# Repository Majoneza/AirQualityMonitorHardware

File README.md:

# AirQualityMonitorHardware

Controller board for measuring indoor air quality with Bluetooth/WiFi connectivity
and an e-ink diplay output.

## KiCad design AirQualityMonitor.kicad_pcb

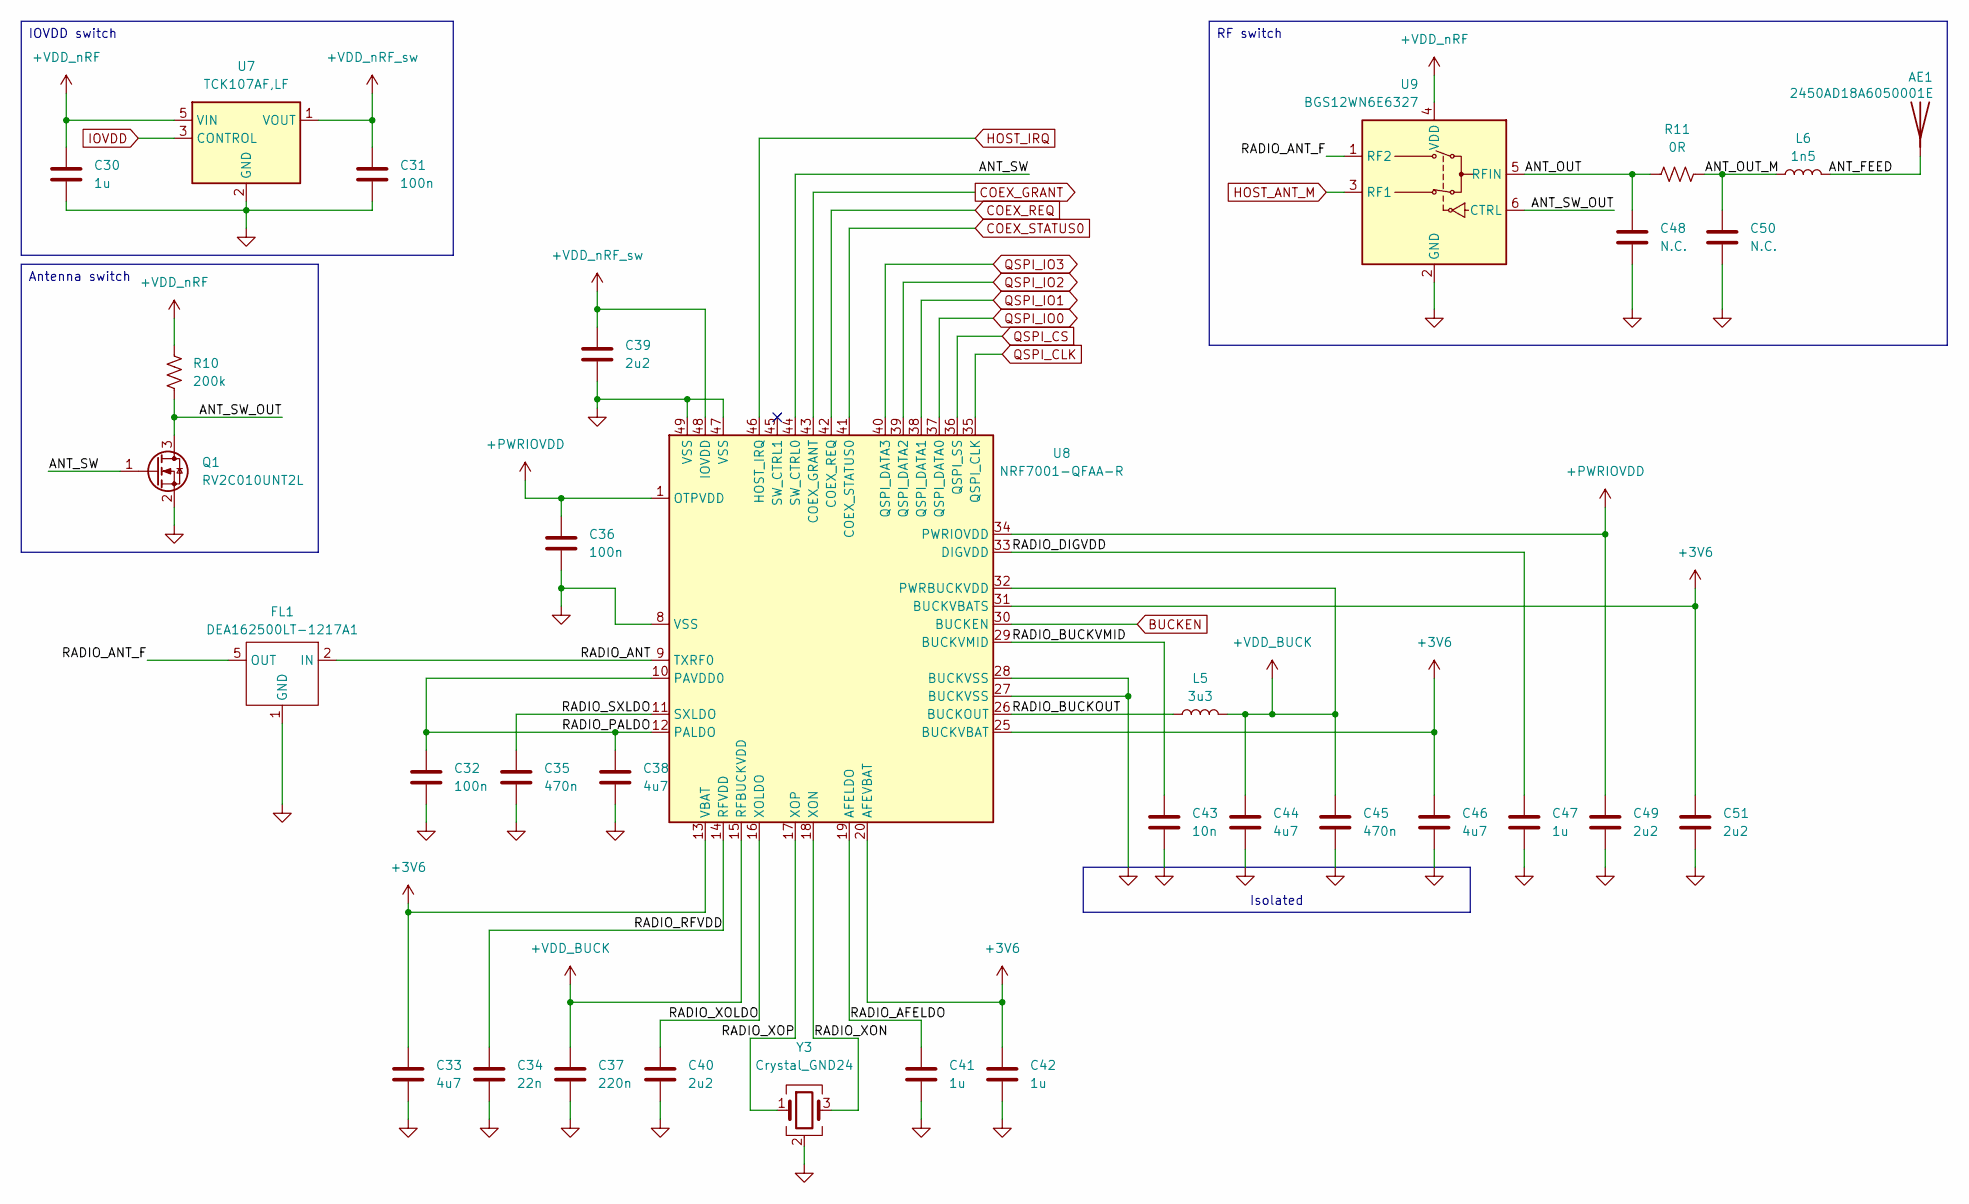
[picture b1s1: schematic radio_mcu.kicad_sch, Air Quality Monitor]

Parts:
AE1: 2450AD18A6050001E; ANTC3216X60N; Mouser Part Number 609-2450AD18A6050001
C30: 1u; C_0402_1005Metric; Manufacturer_Part_Number GRM155Z71A105KE01J; Mouser Part Number 81-GRM155Z71A105KE1J
C31: 100n; C_0603_1608Metric; Manufacturer_Part_Number GCJ188R71C104KA01D; Mouser Part Number 81-GCJ188R71C104KA1D
C32, C36: 100n; C_0201_0603Metric; Part 100nF 16VDC 10% 0201 X7S; Mouser Part Number 81-GRM033C71C104KE4J
C33, C38, C44, C46: 4u7; C_0603_1608Metric; Part 4.7uF 25VDC 10% 0603 X6S; Mouser Part Number 81-GRT188C81E475KE3D
C34: 22n; C_0201_0603Metric; Part 22nF 10VDC 10% 0201 X5R; Mouser Part Number 81-GRT033R61A223KE1J
C35, C45: 470n; C_0201_0603Metric; Part 470nF 6.3VDC 10% 0201 X5R; Mouser Part Number 81-GRM33R60J474KE90D
C37: 220n; C_0201_0603Metric; Part 220nF 10VDC 10% 0201 X5R; Mouser Part Number 81-GRM33R61A224KE90D
C39, C49, C51: 2u2; C_0603_1608Metric; Part 2.2uF 16VDC 10% 0603 X7R; Mouser Part Number 81-GRM188Z71C225KE3D
C40: 2u2; C_0201_0603Metric; Part 2.2uF 10VDC 10% 0201 X5R; Mouser Part Number 81-GRM033R61A225KE7D
C41, C42, C47: 1u; C_0402_1005Metric; Part 1uF 16VDC 10% 0402 X7R; Mouser Part Number 81-GRM155Z71A105KE1J
C43: 10n; C_0201_0603Metric; Part 10nF 16VDC 10% 0201 X7R; Mouser Part Number 81-GRM033R71C103KE4J
C48, C50: N.C.; C_0201_0603Metric
FL1: DEA162500LT-1217A1; DEA162500LT1217A1; Mouser Part Number 810-DEA16250LT1217A1
L5: 3u3; L_1008_2520Metric; Manufacturer_Part_Number LQM2HPN3R3MJ0L; Mouser Part Number 81-LQM2HPN3R3MJ0L
L6: 1n5; L_0201_0603Metric; Manufacturer_Part_Number LQP03HQ1N5B02D; Mouser Part Number 81-LQP03HQ1N5B02D
Q1: RV2C010UNT2L; Manufacturer_Part_Number RV2C010UNT2L; Mouser Part Number 755-RV2C010UNT2L
R10: 200k; R_0805_2012Metric; Manufacturer_Part_Number AC0805FR-7W200KL; Mouser Part Number 603-AC0805FR-7W200KL
R11: 0R; R_0201_0603Metric; Manufacturer_Part_Number RC0201FR-070RL; Mouser Part Number 603-RC0201FR-070RL
U7: TCK107AF,LF; SMV_1; Mouser Part Number 757-TCK107AFLF
U8: NRF7001-QFAA-R; QFN-48-1EP_6x6mm_P0.4mm_EP4.66x4.66mm; Mouser Part Number 949-NRF7001-QFAA-R
U9: BGS12WN6E6327; Infineon_PG-TSNP-6-10_0.7x1.1mm_0.7x1.1mm_P0.4mm; Manufacturer_Part_Number BGS12WN6E6327XTSA1; Mouser Part Number 726-BGS12WN6E6327XTS
Y3: Crystal_GND24; Crystal_SMD_1612-4Pin_1.6x1.2mm; Manufacturer_Part_Number ECS-400-8-47-JTN-TR; Mouser Part Number 520-ECS-400-8-47JTNT

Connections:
+3V6: C33.1, C42.1, C46.1, C51.1, U8.13 (VBAT), U8.20 (AFEVBAT), U8.25 (BUCKVBAT), U8.31 (BUCKVBATS); also elsewhere on the board
+PWRIOVDD: C36.1, C49.1, U8.1 (OTPVDD), U8.34 (PWRIOVDD)
+VDDIO: C30.1, R10.2, U7.5 (VIN), U9.4 (VDD); also elsewhere on the board
+VDD_BUCK: C37.1, C44.1, C45.1, L5.2, U8.15 (RFBUCKVDD), U8.32 (PWRBUCKVDD)
+VDD_nRF_sw: C31.1, C39.1, U7.1 (VOUT), U8.48 (IOVDD)
/Radio MCU/ANT_FEED: AE1.1 (A_1), L6.2
/Radio MCU/ANT_OUT: C48.1, R11.1, U9.5 (RFIN)
/Radio MCU/ANT_OUT_M: C50.1, L6.1, R11.2
/Radio MCU/ANT_SW: Q1.1 (G), U8.44 (SW_CTRL0)
/Radio MCU/ANT_SW_OUT: Q1.3 (D), R10.1, U9.6 (CTRL)
/Radio MCU/RADIO_AFELDO: C41.1, U8.19 (AFELDO)
/Radio MCU/RADIO_ANT: FL1.2 (IN), U8.9 (TXRF0)
/Radio MCU/RADIO_ANT_F: FL1.5 (OUT), U9.1 (RF2)
/Radio MCU/RADIO_BUCKOUT: L5.1, U8.26 (BUCKOUT)
/Radio MCU/RADIO_BUCKVMID: C43.1, U8.29 (BUCKVMID)
/Radio MCU/RADIO_DIGVDD: C47.1, U8.33 (DIGVDD)
/Radio MCU/RADIO_PALDO: C32.1, C38.1, U8.10 (PAVDD0), U8.12 (PALDO)
/Radio MCU/RADIO_RFVDD: C34.1, U8.14 (RFVDD)
/Radio MCU/RADIO_SXLDO: C35.1, U8.11 (SXLDO)
/Radio MCU/RADIO_XOLDO: C40.1, U8.16 (XOLDO)
/Radio MCU/RADIO_XON: U8.18 (XON), Y3.3
/Radio MCU/RADIO_XOP: U8.17 (XOP), Y3.1
BUCKEN: U8.30 (BUCKEN); also elsewhere on the board
COEX_GRANT: U8.43 (COEX_GRANT); also elsewhere on the board
COEX_REQ: U8.42 (COEX_REQ); also elsewhere on the board
COEX_STATUS0: U8.41 (COEX_STATUS0); also elsewhere on the board
GND: C30.2, C31.2, C32.2, C33.2, C34.2, C35.2, C36.2, C37.2, C38.2, C39.2, C40.2, C41.2, C42.2, C43.2, C44.2, C45.2, C46.2, C47.2, C48.2, C49.2, C50.2, C51.2, FL1.1 (GND), FL1.3 (GND), FL1.4 (GND), FL1.6 (GND), Q1.2 (S), U7.2 (GND), U8.8 (VSS), U8.27 (BUCKVSS), U8.28 (BUCKVSS), U8.47 (VSS), U8.49 (VSS), U9.2 (GND), Y3.2 (G), Y3.4 (G); also elsewhere on the board
HOST_ANT_M: U9.3 (RF1); also elsewhere on the board
HOST_IRQ: U8.46 (HOST_IRQ); also elsewhere on the board
IOVDD: U7.3 (CONTROL); also elsewhere on the board
QSPI_CLK: U8.35 (QSPI_CLK); also elsewhere on the board
QSPI_CS: U8.36 (QSPI_SS); also elsewhere on the board
QSPI_IO0: U8.37 (QSPI_DATA0); also elsewhere on the board
QSPI_IO1: U8.38 (QSPI_DATA1); also elsewhere on the board
QSPI_IO2: U8.39 (QSPI_DATA2); also elsewhere on the board
QSPI_IO3: U8.40 (QSPI_DATA3); also elsewhere on the board

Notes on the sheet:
RF switch
Antenna switch
Isolated
IOVDD switch

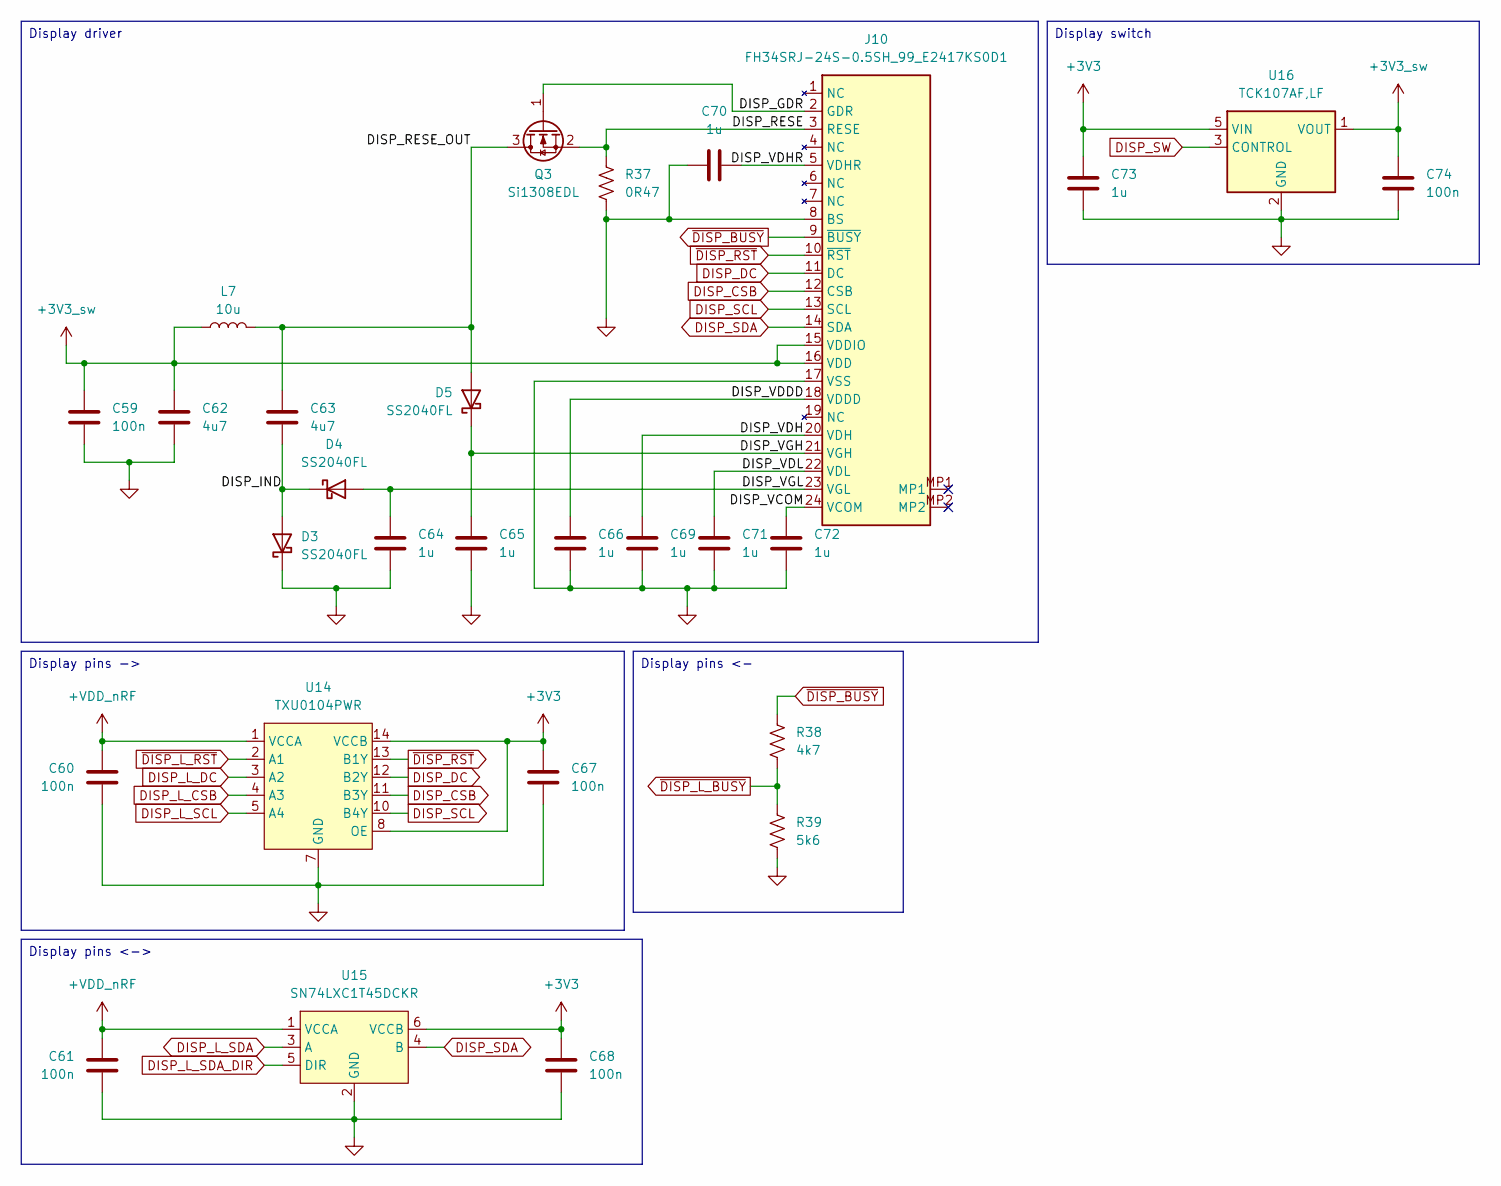
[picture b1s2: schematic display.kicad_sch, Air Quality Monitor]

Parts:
C59: 100n; C_0603_1608Metric; Part 100nF 16VDC 10% 0603 X7R; Mouser Part Number 81-GCJ188R71C104KA1D
C60, C61, C67, C68, C74: 100n; C_0603_1608Metric; Manufacturer_Part_Number GCJ188R71C104KA01D; Mouser Part Number 81-GCJ188R71C104KA1D
C62, C63: 4u7; C_0603_1608Metric; Part 4.7uF 25VDC 10% 0603 X6S; Mouser Part Number 81-GRT188C81E475KE3D
C64, C65, C66, C69, C70, C71, C72: 1u; C_0603_1608Metric; Part 1uF 25VDC 10% 0603 X5R; Mouser Part Number 603-CC603KRX5R8BB105
C73: 1u; C_0402_1005Metric; Manufacturer_Part_Number GRM155Z71A105KE01J; Mouser Part Number 81-GRM155Z71A105KE1J
D3, D4, D5: SS2040FL; D_SOD-123F; Manufacturer_Part_Number SS2040FL_R1_00001; Mouser Part Number 241-SS2040FLR100001
J10: FH34SRJ-24S-0.5SH_99_E2417KS0D1; FH34SRJ24S05SH99; Mouser Part Number 798-FH34SRJ24S05SH99
L7: 10u; L_1008_2520Metric; Manufacturer_Part_Number AOTA-N252010S-100MT; Mouser Part Number 815-AOTAN252010S100M
Q3: Si1308EDL; SOT-323_SC-70; Manufacturer_Part_Number SI1308EDL-T1-GE3; Mouser Part Number 78-SI1308EDL-T1-GE3
R37: 0R47; R_0603_1608Metric; Manufacturer_Part_Number RCWL0603R470JNEA; Mouser Part Number 71-RCWL0603R470JNEA
R38: 4k7; R_0402_1005Metric; Manufacturer_Part_Number RC0402JR-104K7L; Mouser Part Number 603-RC0402JR-104K7L
R39: 5k6; R_0402_1005Metric; Manufacturer_Part_Number RC0402JR-075K6L; Mouser Part Number 603-RC0402JR-075K6L
U14: TXU0104PWR; TSSOP-14_4.4x5mm_P0.65mm; Mouser Part Number 595-TXU0104PWR
U15: SN74LXC1T45DCKR; SOT-363_SC-70-6; Mouser Part Number 595-SN74LXC1T45DCKR
U16: TCK107AF,LF; SMV_1; Mouser Part Number 757-TCK107AFLF

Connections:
+3V3: C67.1, C68.1, C73.1, U14.8 (OE), U14.14 (VCCB), U15.6 (VCCB), U16.5 (VIN); also elsewhere on the board
+3V3_sw: C59.1, C62.1, C74.1, J10.15 (VDDIO), J10.16 (VDD), L7.1, U16.1 (VOUT)
+VDDIO: C60.1, C61.1, U14.1 (VCCA), U15.1 (VCCA); also elsewhere on the board
/Display/DISP_GDR: J10.2 (GDR), Q3.1 (G)
/Display/DISP_IND: C63.2, D3.2 (A), D4.1 (K)
/Display/DISP_RESE: J10.3 (RESE), Q3.2 (S), R37.1
/Display/DISP_RESE_OUT: C63.1, D5.2 (A), L7.2, Q3.3 (D)
/Display/DISP_VCOM: C72.1, J10.24 (VCOM)
/Display/DISP_VDDD: C66.1, J10.18 (VDDD)
/Display/DISP_VDH: C69.1, J10.20 (VDH)
/Display/DISP_VDHR: C70.2, J10.5 (VDHR)
/Display/DISP_VDL: C71.1, J10.22 (VDL)
/Display/DISP_VGH: C65.1, D5.1 (K), J10.21 (VGH)
/Display/DISP_VGL: C64.1, D4.2 (A), J10.23 (VGL)
DISP_CSB: J10.12 (CSB), U14.11 (B3Y)
DISP_DC: J10.11 (DC), U14.12 (B2Y)
DISP_L_CSB: U14.4 (A3); also elsewhere on the board
DISP_L_DC: U14.3 (A2); also elsewhere on the board
DISP_L_SCL: U14.5 (A4); also elsewhere on the board
DISP_L_SDA: U15.3 (A); also elsewhere on the board
DISP_L_SDA_DIR: U15.5 (DIR); also elsewhere on the board
DISP_SCL: J10.13 (SCL), U14.10 (B4Y)
DISP_SDA: J10.14 (SDA), U15.4 (B)
DISP_SW: U16.3 (CONTROL); also elsewhere on the board
GND: C59.2, C60.2, C61.2, C62.2, C64.2, C65.2, C66.2, C67.2, C68.2, C69.2, C70.1, C71.2, C72.2, C73.2, C74.2, D3.1 (K), J10.8 (BS), J10.17 (VSS), R37.2, R39.2, U14.7 (GND), U15.2 (GND), U16.2 (GND); also elsewhere on the board
~DISP_BUSY: J10.9 (~BUSY), R38.1
~DISP_L_BUSY: R38.2, R39.1; also elsewhere on the board
~DISP_L_RST: U14.2 (A1); also elsewhere on the board
~DISP_RST: J10.10 (~RST), U14.13 (B1Y)

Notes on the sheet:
Display pins <->
Display pins ->
Display pins <-
Display driver
Display switch

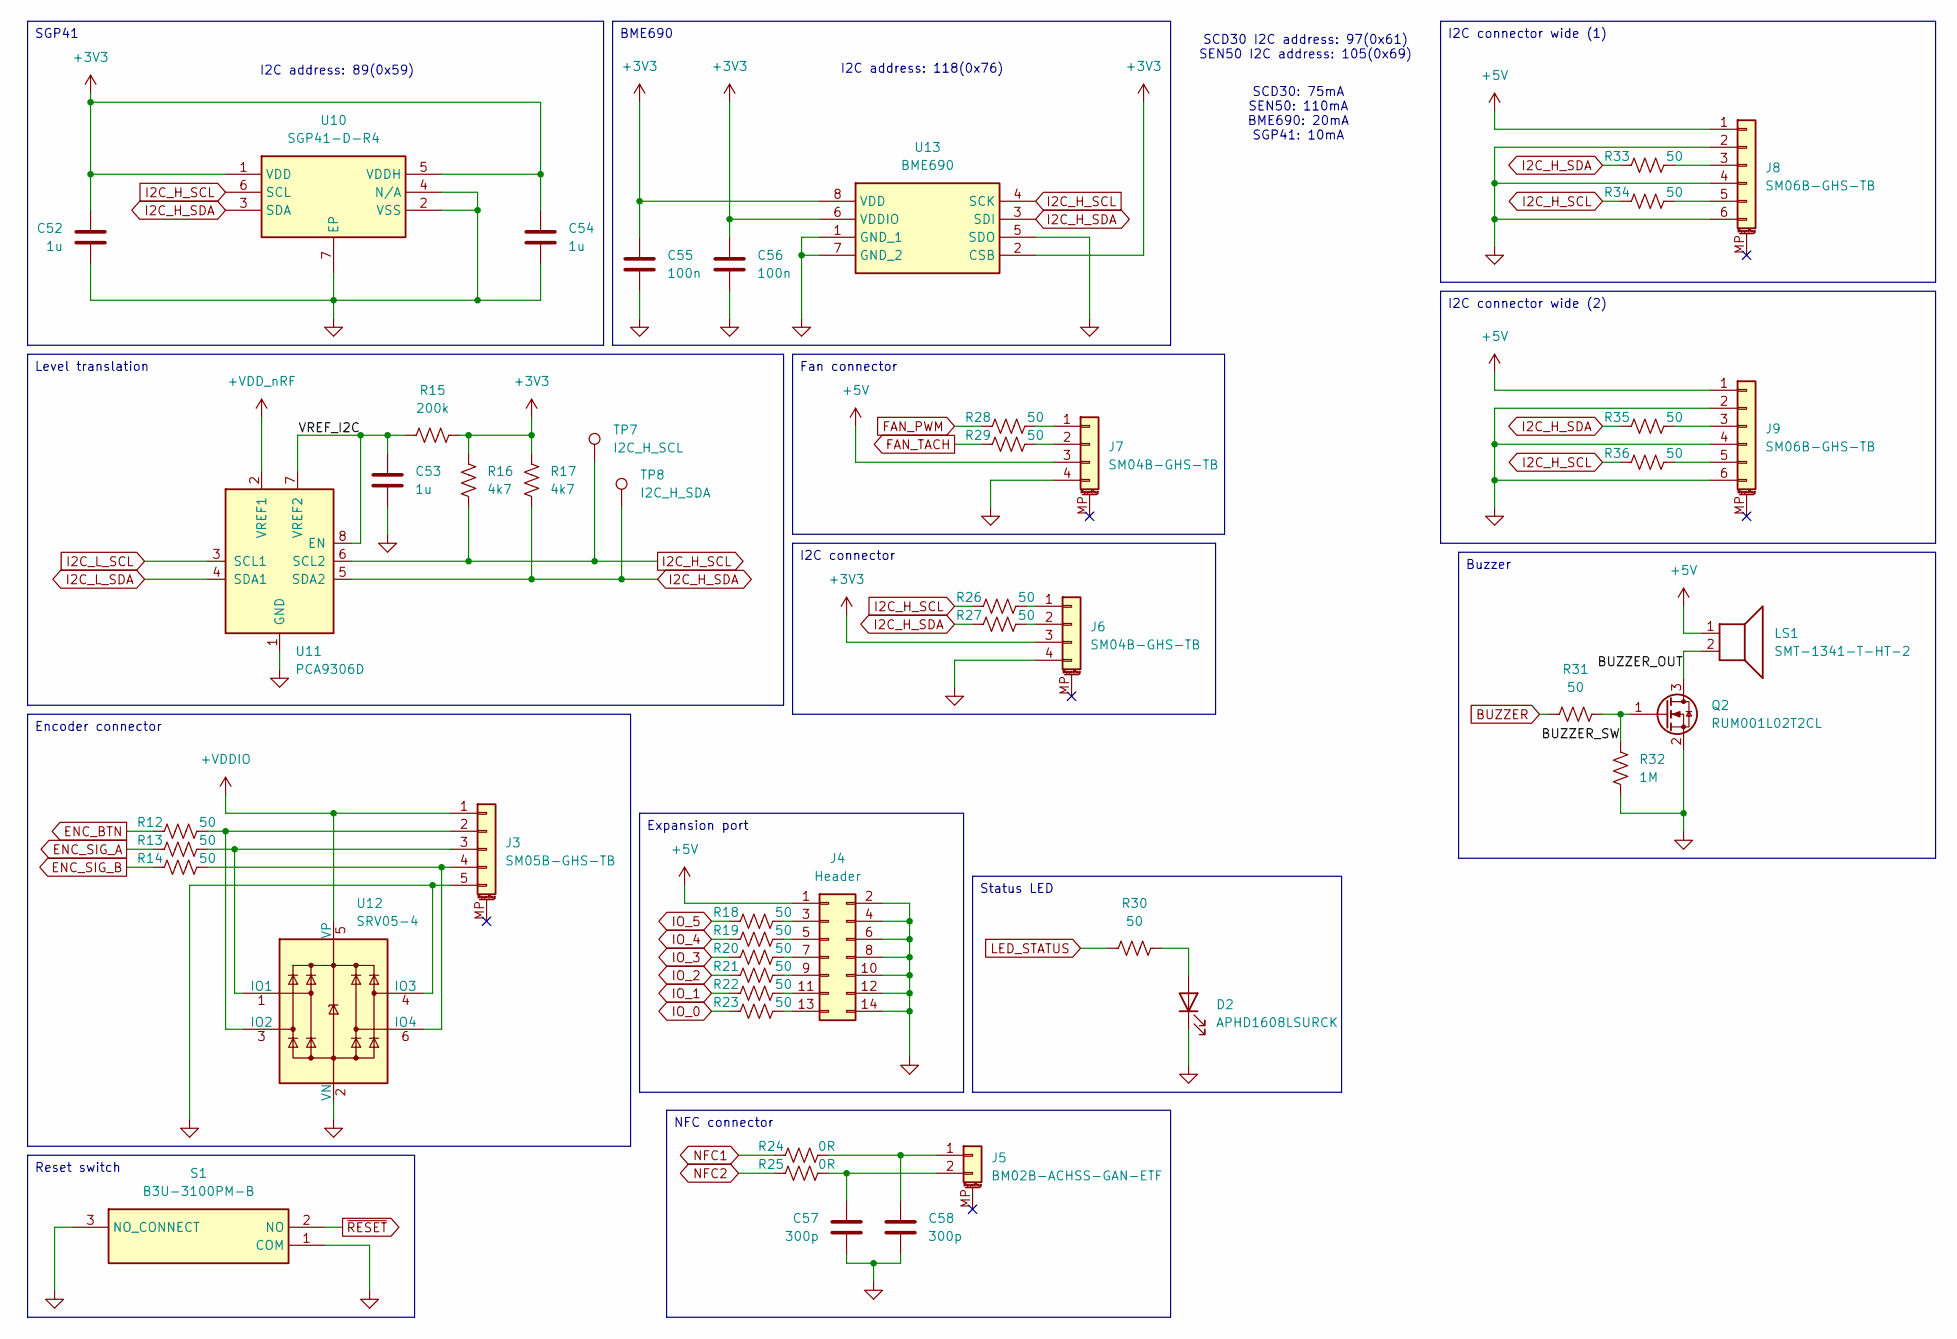
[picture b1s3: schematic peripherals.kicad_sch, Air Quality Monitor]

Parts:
C52, C53, C54: 1u; C_0402_1005Metric; Manufacturer_Part_Number GRM155Z71A105KE01J; Mouser Part Number 81-GRM155Z71A105KE1J
C55, C56: 100n; C_0201_0603Metric; Part 100nF 16VDC 10% 0201 X7S; Mouser Part Number 81-GRM033C71C104KE4J
C57, C58: 300p; C_0402_1005Metric; Manufacturer_Part_Number GRM1555C1H301JA01D; Mouser Part Number 81-GRM1555C1H301JA1D
D2: APHD1608LSURCK; LED_0603_1608Metric; Mouser Part Number 604-APHD1608LSURCK
J3: SM05B-GHS-TB; JST_GH_SM05B-GHS-TB_1x05-1MP_P1.25mm_Horizontal; Manufacturer_Part_Number SM05B-GHS-TB(LF)(SN); Mouser Part Number 306-SM05BGHSTBLFSN
J4: Header; PinSocket_2x07_P1.27mm_Vertical_SMD
J5: BM02B-ACHSS-GAN-ETF; JST_ACH_BM02B-ACHSS-GAN-ETF_1x02-1MP_P1.20mm_Vertical; Manufacturer_Part_Number BM02B-ACHSS-GAN-ETF(LF)(SN); Mouser Part Number 306-2BACHSSGANETFL
J6, J7: SM04B-GHS-TB; JST_GH_SM04B-GHS-TB_1x04-1MP_P1.25mm_Horizontal; Manufacturer_Part_Number SM04B-GHS-TB(LF)(SN); Mouser Part Number 306-SM04BGHSTBLFSN
J8, J9: SM06B-GHS-TB; JST_GH_SM06B-GHS-TB_1x06-1MP_P1.25mm_Horizontal; Manufacturer_Part_Number SM06B-GHS-TB(LF)(SN); Mouser Part Number 306-SM06BGHSTBLFSN
LS1: SMT-1341-T-HT-2; SMT1341THT2; Mouser Part Number 665-SMT-1341-T-HT-2
Q2: RUM001L02T2CL; SOT723; Mouser Part Number 755-RUM001L02T2CL
R12, R13, R14, R18, R19, R20, R21, R22, R23, R26, R27, R28, R29, R30, R31, R33, R34, R35, R36: 50; R_0402_1005Metric; Manufacturer_Part_Number RC0402JR-0750RL; Mouser Part Number 603-RC0402JR-0750RL
R15: 200k; R_0805_2012Metric; Manufacturer_Part_Number AC0805FR-7W200KL; Mouser Part Number 603-AC0805FR-7W200KL
R16, R17: 4k7; R_0402_1005Metric; Manufacturer_Part_Number RC0402JR-104K7L; Mouser Part Number 603-RC0402JR-104K7L
R24, R25: 0R; R_0603_1608Metric; Manufacturer_Part_Number ERJ-S030R00V; Mouser Part Number 667-ERJ-S030R00V
R32: 1M; R_0603_1608Metric; Manufacturer_Part_Number RT0603BRD071ML; Mouser Part Number 603-RT0603BRD071ML
S1: B3U-3100PM-B; B3U3100PMB; Mouser Part Number 653-B3U-3100PM-B
TP7: I2C_H_SCL; TestPoint_Pad_D1.0mm
TP8: I2C_H_SDA; TestPoint_Pad_D1.0mm
U10: SGP41-D-R4; SON80P244X244X95-7N; Mouser Part Number 403-SGP41-D-R4
U11: PCA9306D; TSSOP-8_3x3mm_P0.65mm; Manufacturer_Part_Number PCA9306DP,118; Mouser Part Number 771-PCA9306DP-T
U12: SRV05-4; SOT-23-6; Manufacturer_Part_Number SRV05-4.TCT; Mouser Part Number 947-SRV05-4.TCT
U13: BME690; Mouser Part Number 262-BME690

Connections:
+3V3: C52.1, C54.1, C55.1, C56.1, J6.3, R15.2, R16.1, R17.1, U10.1 (VDD), U10.5 (VDDH), U13.2 (CSB), U13.6 (VDDIO), U13.8 (VDD); also elsewhere on the board
+5V: J4.1, J7.3, J8.1, J9.1, LS1.1; also elsewhere on the board
+VDDIO: J3.1, U11.2 (VREF1), U12.5 (VP); also elsewhere on the board
/Peripherals/BUZZER_OUT: LS1.2, Q2.3 (D)
/Peripherals/BUZZER_SW: Q2.1 (G), R31.2, R32.2
/Peripherals/VREF_I2C: C53.1, R15.1, U11.7 (VREF2), U11.8 (EN)
BUZZER: R31.1; also elsewhere on the board
ENC_BTN: R12.1; also elsewhere on the board
ENC_SIG_A: R13.1; also elsewhere on the board
ENC_SIG_B: R14.1; also elsewhere on the board
FAN_PWM: R28.1; also elsewhere on the board
FAN_TACH: R29.1; also elsewhere on the board
GND: C52.2, C53.2, C54.2, C55.2, C56.2, C57.2, C58.2, D2.1 (K), J3.5, J4.2, J4.4, J4.6, J4.8, J4.10, J4.12, J4.14, J6.4, J7.4, J8.2, J8.4, J8.6, J9.2, J9.4, J9.6, Q2.2 (S), R32.1, S1.1 (COM), S1.3 (NO_CONNECT), U10.2 (VSS), U10.4 (N/A), U10.7 (EP), U11.1 (GND), U12.2 (VN), U12.4 (IO3), U13.1 (GND_1), U13.5 (SDO), U13.7 (GND_2); also elsewhere on the board
I2C_H_SCL: R16.2, R26.1, R34.1, R36.1, TP7.1 (1_1), U10.6 (SCL), U11.6 (SCL2), U13.4 (SCK)
I2C_H_SDA: R17.2, R27.1, R33.1, R35.1, TP8.1 (1_1), U10.3 (SDA), U11.5 (SDA2), U13.3 (SDI)
I2C_L_SCL: U11.3 (SCL1); also elsewhere on the board
I2C_L_SDA: U11.4 (SDA1); also elsewhere on the board
IO_0: R23.1; also elsewhere on the board
IO_1: R22.1; also elsewhere on the board
IO_2: R21.1; also elsewhere on the board
IO_3: R20.1; also elsewhere on the board
IO_4: R19.1; also elsewhere on the board
IO_5: R18.1; also elsewhere on the board
LED_STATUS: R30.1; also elsewhere on the board
NFC1: R24.1; also elsewhere on the board
NFC2: R25.1; also elsewhere on the board
unnamed: D2.2 (A), R30.2
unnamed: J3.2, R12.2, U12.3 (IO2)
unnamed: J3.3, R13.2, U12.1 (IO1)
unnamed: J3.4, R14.2, U12.6 (IO4)
unnamed: J4.3, R18.2
unnamed: J4.5, R19.2
unnamed: J4.7, R20.2
unnamed: J4.9, R21.2
unnamed: J4.11, R22.2
unnamed: J4.13, R23.2
unnamed: C58.1, J5.1, R24.2
unnamed: C57.1, J5.2, R25.2
unnamed: J6.1, R26.2
unnamed: J6.2, R27.2
unnamed: J7.1, R28.2
unnamed: J7.2, R29.2
unnamed: J8.3, R33.2
unnamed: J8.5, R34.2
unnamed: J9.3, R35.2
unnamed: J9.5, R36.2
~RESET: S1.2 (NO); also elsewhere on the board

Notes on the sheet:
SCD30 I2C address: 97(0x61) SEN50 I2C address: 105(0x69)
I2C address: 118(0x76)
SCD30: 75mA SEN50: 110mA BME690: 20mA SGP41: 10mA
I2C address: 89(0x59)
Encoder connector
Reset switch
Buzzer
Level translation
SGP41
I2C connector
Status LED
NFC connector
I2C connector wide (2)
Fan connector
Expansion port
BME690
I2C connector wide (1)

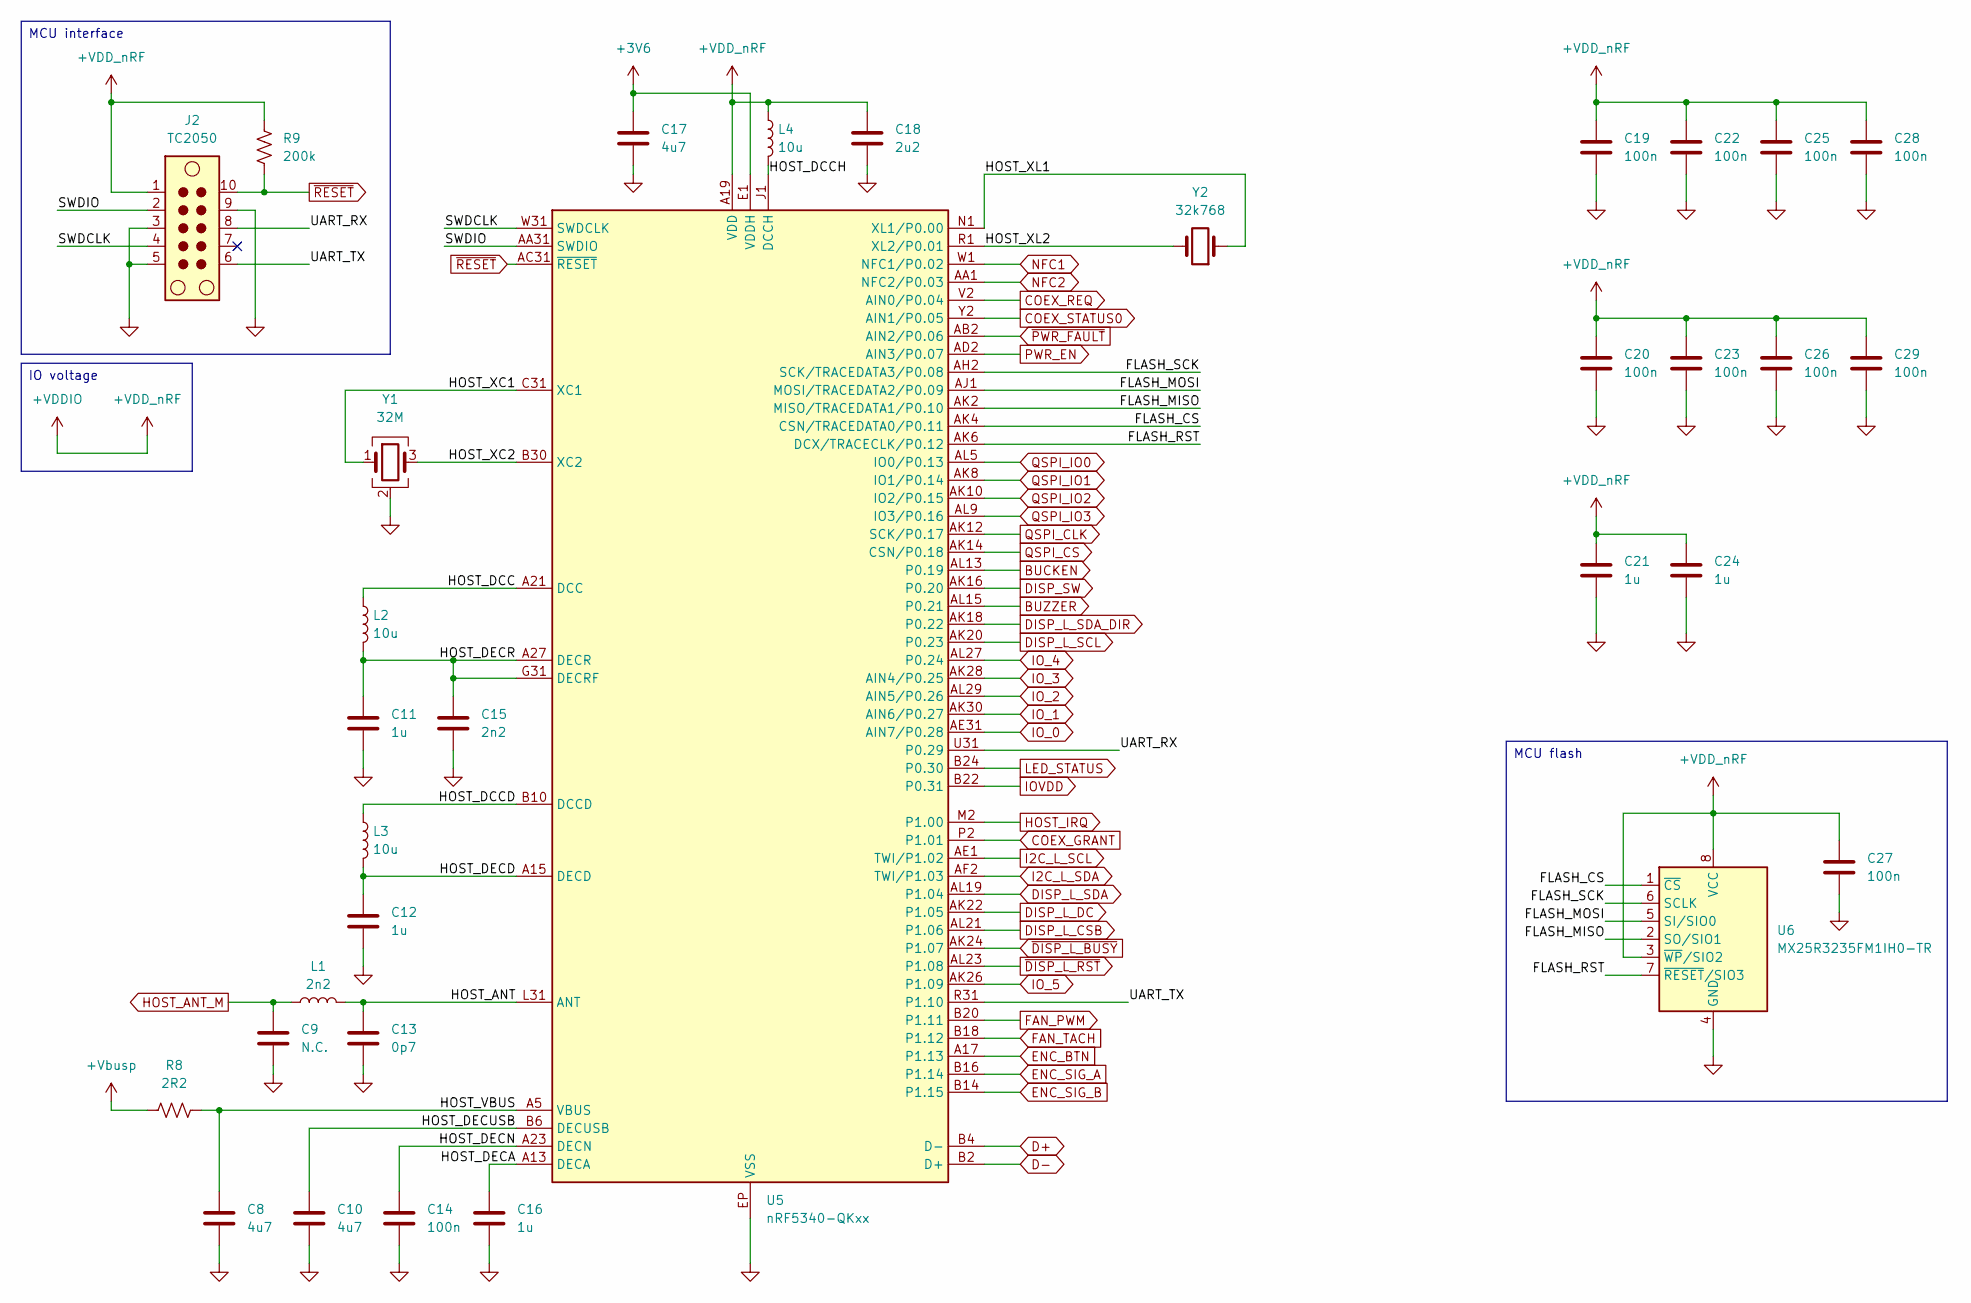
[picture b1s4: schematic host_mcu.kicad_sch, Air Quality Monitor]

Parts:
C8, C10, C17: 4u7; C_0603_1608Metric; Part 4.7uF 16VDC 10% 0603 X7R; Mouser Part Number 81-GRM188Z71C475KE1J
C9: N.C.; C_0201_0603Metric
C11, C12, C16, C21, C24: 1u; C_0402_1005Metric; Part 1uF 16VDC 10% 0402 X7R; Mouser Part Number 81-GRM155Z71A105KE1J
C13: 0p7; C_0201_0603Metric; Part 0.7pF 25VDC 8% 0201 NP0; Mouser Part Number 603-CQ201ARNPO8BNR70
C14, C19, C20, C22, C23, C25, C26, C27, C28, C29: 100n; C_0201_0603Metric; Part 100nF 16VDC 10% 0201 X7S; Mouser Part Number 81-GRM033C71C104KE4J
C15: 2n2; C_0201_0603Metric; Part 2.2nF 16VDC 10% 0201 X7R; Mouser Part Number 603-CC201KRX7R7BB222
C18: 2u2; C_0603_1608Metric; Part 2.2uF 16VDC 10% 0603 X7R; Mouser Part Number 81-GRM188Z71C225KE3D
J2: TC2050; Tag-Connect_TC2050-IDC-FP_2x05_P1.27mm_Vertical
L1: 2n2; L_0201_0603Metric; Manufacturer_Part_Number L02012R2BHSTR; Mouser Part Number 581-L02012R2BHSTR
L2, L3, L4: 10u; L_0603_1608Metric; Manufacturer_Part_Number MLZ1608E100MT; Mouser Part Number 810-MLZ1608E100MT
R8: 2R2; R_0201_0603Metric; Manufacturer_Part_Number AC0201FR-072R2L; Mouser Part Number 603-AC0201FR-072R2L
R9: 200k; R_0805_2012Metric; Manufacturer_Part_Number AC0805FR-7W200KL; Mouser Part Number 603-AC0805FR-7W200KL
U5: nRF5340-QKxx; Nordic_AQFN-94-1EP_7x7mm_P0.4mm; Manufacturer_Part_Number nRF5340-QKAA-R7; Mouser Part Number 949-NRF5340-QKAA-R7
U6: MX25R3235FM1IH0-TR; JEITA_SOIC-8_3.9x4.9mm_P1.27mm; Manufacturer_Part_Number MX25R3235FM1IH0-TR; Mouser Part Number 95-25R3235FM1IH0TR
Y1: 32M; Crystal_SMD_2016-4Pin_2.0x1.6mm; Manufacturer_Part_Number ECS-320-8-37B-CWY-TR3; Mouser Part Number 520-ECS320837BCWYTR3
Y2: 32k768; Crystal_SMD_3215-2Pin_3.2x1.5mm; Manufacturer_Part_Number ECS-.327-9-34B-TR; Mouser Part Number 520-ECS-.327-9-34B-T

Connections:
+3V6: C17.1, U5.E1 (VDDH); also elsewhere on the board
+VDDIO: C18.1, C19.1, C20.1, C21.1, C22.1, C23.1, C24.1, C25.1, C26.1, C27.1, C28.1, C29.1, J2.1, L4.1, R9.2, U5.A19 (VDD), U5.AC1 (VDD), U5.AG1 (VDD), U5.AJ31 (VDD), U5.AL3 (VDD), U5.AL7 (VDD), U5.AL11 (VDD), U5.AL17 (VDD), U5.AL25 (VDD), U5.B8 (VDD), U5.B28 (VDD), U5.C1 (VDD), U5.E31 (VDD), U5.L1 (VDD), U5.N31 (VDD), U5.U1 (VDD), U6.3 (~WP/SIO2), U6.8 (VCC); also elsewhere on the board
+Vbusp: R8.1; also elsewhere on the board
/Host MCU/FLASH_CS: U5.AK4 (CSN/TRACEDATA0/P0.11), U6.1 (~CS)
/Host MCU/FLASH_MISO: U5.AK2 (MISO/TRACEDATA1/P0.10), U6.2 (SO/SIO1)
/Host MCU/FLASH_MOSI: U5.AJ1 (MOSI/TRACEDATA2/P0.09), U6.5 (SI/SIO0)
/Host MCU/FLASH_RST: U5.AK6 (DCX/TRACECLK/P0.12), U6.7 (~RESET/SIO3)
/Host MCU/FLASH_SCK: U5.AH2 (SCK/TRACEDATA3/P0.08), U6.6 (SCLK)
/Host MCU/HOST_ANT: C13.1, L1.2, U5.L31 (ANT)
/Host MCU/HOST_DCC: L2.1, U5.A21 (DCC)
/Host MCU/HOST_DCCD: L3.1, U5.B10 (DCCD)
/Host MCU/HOST_DCCH: L4.2, U5.J1 (DCCH)
/Host MCU/HOST_DECA: C16.1, U5.A13 (DECA)
/Host MCU/HOST_DECD: C12.1, L3.2, U5.A15 (DECD)
/Host MCU/HOST_DECN: C14.1, U5.A23 (DECN)
/Host MCU/HOST_DECR: C11.1, C15.1, L2.2, U5.A27 (DECR), U5.G31 (DECRF)
/Host MCU/HOST_DECUSB: C10.1, U5.B6 (DECUSB)
/Host MCU/HOST_VBUS: C8.1, R8.2, U5.A5 (VBUS)
/Host MCU/HOST_XC1: U5.C31 (XC1), Y1.1
/Host MCU/HOST_XC2: U5.B30 (XC2), Y1.3
/Host MCU/HOST_XL1: U5.N1 (XL1/P0.00), Y2.1
/Host MCU/HOST_XL2: U5.R1 (XL2/P0.01), Y2.2
/Host MCU/SWDCLK: J2.4, U5.W31 (SWDCLK)
/Host MCU/SWDIO: J2.2, U5.AA31 (SWDIO)
/Host MCU/UART_RX: J2.8, U5.U31 (P0.29)
/Host MCU/UART_TX: J2.6, U5.R31 (P1.10)
BUCKEN: U5.AL13 (P0.19); also elsewhere on the board
BUZZER: U5.AL15 (P0.21); also elsewhere on the board
COEX_GRANT: U5.P2 (P1.01); also elsewhere on the board
COEX_REQ: U5.V2 (AIN0/P0.04); also elsewhere on the board
COEX_STATUS0: U5.Y2 (AIN1/P0.05); also elsewhere on the board
D+: U5.B4 (D-); also elsewhere on the board
D-: U5.B2 (D+); also elsewhere on the board
DISP_L_CSB: U5.AL21 (P1.06); also elsewhere on the board
DISP_L_DC: U5.AK22 (P1.05); also elsewhere on the board
DISP_L_SCL: U5.AK20 (P0.23); also elsewhere on the board
DISP_L_SDA: U5.AL19 (P1.04); also elsewhere on the board
DISP_L_SDA_DIR: U5.AK18 (P0.22); also elsewhere on the board
DISP_SW: U5.AK16 (P0.20); also elsewhere on the board
ENC_BTN: U5.A17 (P1.13); also elsewhere on the board
ENC_SIG_A: U5.B16 (P1.14); also elsewhere on the board
ENC_SIG_B: U5.B14 (P1.15); also elsewhere on the board
FAN_PWM: U5.B20 (P1.11); also elsewhere on the board
FAN_TACH: U5.B18 (P1.12); also elsewhere on the board
GND: C8.2, C9.2, C10.2, C11.2, C12.2, C13.2, C14.2, C15.2, C16.2, C17.2, C18.2, C19.2, C20.2, C21.2, C22.2, C23.2, C24.2, C25.2, C26.2, C27.2, C28.2, C29.2, J2.3, J2.5, J2.9, U5.A25 (VSS), U5.B12 (VSS), U5.B26 (VSS), U5.EP (VSS), U5.G1 (VSS), U5.H2 (VSS), U5.J31 (VSS), U6.4 (GND), Y1.2 (G), Y1.4 (G); also elsewhere on the board
HOST_ANT_M: C9.1, L1.1; also elsewhere on the board
HOST_IRQ: U5.M2 (P1.00); also elsewhere on the board
I2C_L_SCL: U5.AE1 (TWI/P1.02); also elsewhere on the board
I2C_L_SDA: U5.AF2 (TWI/P1.03); also elsewhere on the board
IOVDD: U5.B22 (P0.31); also elsewhere on the board
IO_0: U5.AE31 (AIN7/P0.28); also elsewhere on the board
IO_1: U5.AK30 (AIN6/P0.27); also elsewhere on the board
IO_2: U5.AL29 (AIN5/P0.26); also elsewhere on the board
IO_3: U5.AK28 (AIN4/P0.25); also elsewhere on the board
IO_4: U5.AL27 (P0.24); also elsewhere on the board
IO_5: U5.AK26 (P1.09); also elsewhere on the board
LED_STATUS: U5.B24 (P0.30); also elsewhere on the board
NFC1: U5.W1 (NFC1/P0.02); also elsewhere on the board
NFC2: U5.AA1 (NFC2/P0.03); also elsewhere on the board
PWR_EN: U5.AD2 (AIN3/P0.07); also elsewhere on the board
QSPI_CLK: U5.AK12 (SCK/P0.17); also elsewhere on the board
QSPI_CS: U5.AK14 (CSN/P0.18); also elsewhere on the board
QSPI_IO0: U5.AL5 (IO0/P0.13); also elsewhere on the board
QSPI_IO1: U5.AK8 (IO1/P0.14); also elsewhere on the board
QSPI_IO2: U5.AK10 (IO2/P0.15); also elsewhere on the board
QSPI_IO3: U5.AL9 (IO3/P0.16); also elsewhere on the board
~DISP_L_BUSY: U5.AK24 (P1.07); also elsewhere on the board
~DISP_L_RST: U5.AL23 (P1.08); also elsewhere on the board
~PWR_FAULT: U5.AB2 (AIN2/P0.06); also elsewhere on the board
~RESET: J2.10, R9.1, U5.AC31 (~RESET); also elsewhere on the board

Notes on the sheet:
MCU interface
MCU flash
IO voltage
